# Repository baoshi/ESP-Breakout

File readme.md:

# ESP-Breakout

Breadboard adapter for ESP-07 and ESP-12 full I/O ESP8266 module

Licensed under CC-0, available at http://creativecommons.org/publicdomain/zero/1.0/

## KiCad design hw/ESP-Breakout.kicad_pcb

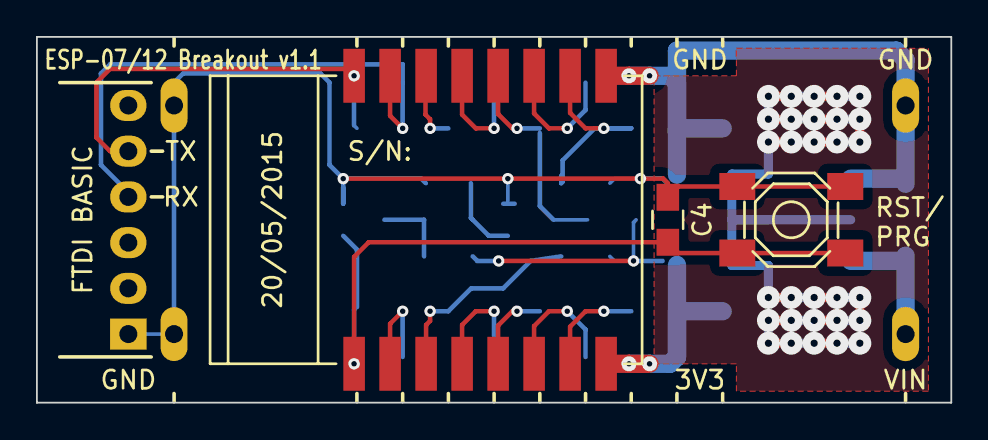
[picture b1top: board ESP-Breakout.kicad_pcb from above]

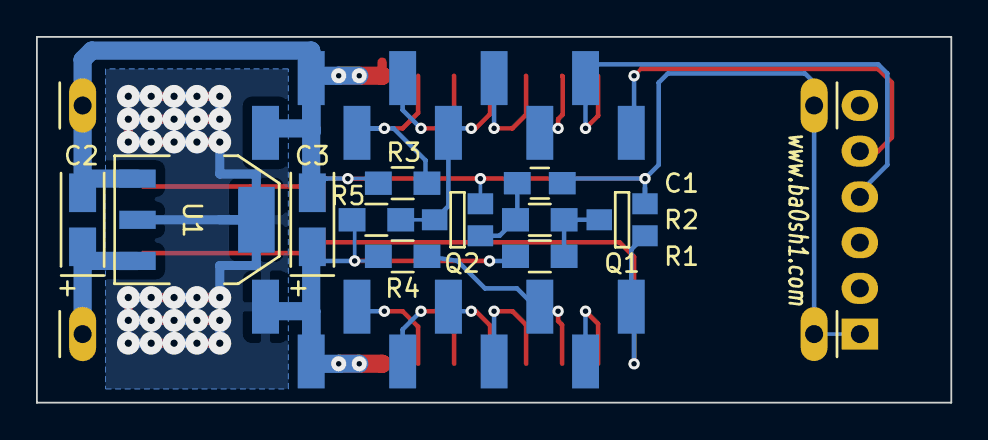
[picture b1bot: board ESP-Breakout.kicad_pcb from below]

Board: 2 copper layers, 50.8 x 20.3 mm, 17 parts (13 on the bottom side), 19 nets.

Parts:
C1: 2u2; C_0805_HandSoldering
C2: 4u7; TantalC_SizeA_EIA-3216_Wave
C3: 22u; TantalC_SizeA_EIA-3216_Wave
C4: 0.1u; C_0805_HandSoldering
M1: ESP-07
P1: FTDI BASIC; Pin_Header_Angled_1x06
P2: CONN_01X11; SMD-PINHEADER-11A
P3: CONN_01X11; SMD-PINHEADER-11B
Q1, Q2: BSS138; SOT-23-GDS
R1: 470K; R_0805_HandSoldering
R2: 100K; R_0805_HandSoldering
R3, R5: 10K; R_0805_HandSoldering
R4: 47K; R_0805_HandSoldering
SW1: SW_PUSH; PUSH_4x4_SMD
U1: 1117-3.3; SOT-223

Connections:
+3V3: C3.1, M1.8, P3.9, P3.10, R1.1, R4.2, R5.2, U1.2
+5V: C2.1, P3.11, U1.3
/GPIO0: M1.12, P2.6, Q2.D, R5.1
/RESET: C4.1, M1.1, P3.2, Q1.G, SW1.2
/RXI: M1.16, P1.5, P2.2
/TXO: M1.15, P1.4, P2.3
GND: C1.2, C2.2, C3.2, C4.2, M1.9, P1.1, P2.1, P2.9, P2.10, P2.11, P3.1, Q1.S, Q2.S, R3.1, SW1.1, U1.1
unnamed: C1.1, Q2.G, R2.1
unnamed: M1.2, P3.3
unnamed: M1.3, P3.4, R4.1
unnamed: M1.4, P3.5
unnamed: M1.5, P3.6
unnamed: M1.6, P3.7
unnamed: M1.7, P3.8
unnamed: M1.10, P2.8, R3.2
unnamed: M1.11, P2.7
unnamed: M1.13, P2.5
unnamed: M1.14, P2.4
unnamed: Q1.D, R1.2, R2.2

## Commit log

2015-01-30 :space_invader: Added .gitattributes
2015-02-15 Footprint change
    Footprint change to facilitate hand soldering
2015-03-28 Minor footprint change to Tantalum caps
2015-08-20 V1.1
    Added a pull-up resistor on GPIO0 pin
2017-04-17 Fix broken Markdown headings
